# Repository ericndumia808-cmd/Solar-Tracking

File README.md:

solar tracking system
designs by eric

## Collaborators
1. Masika - Supervisor

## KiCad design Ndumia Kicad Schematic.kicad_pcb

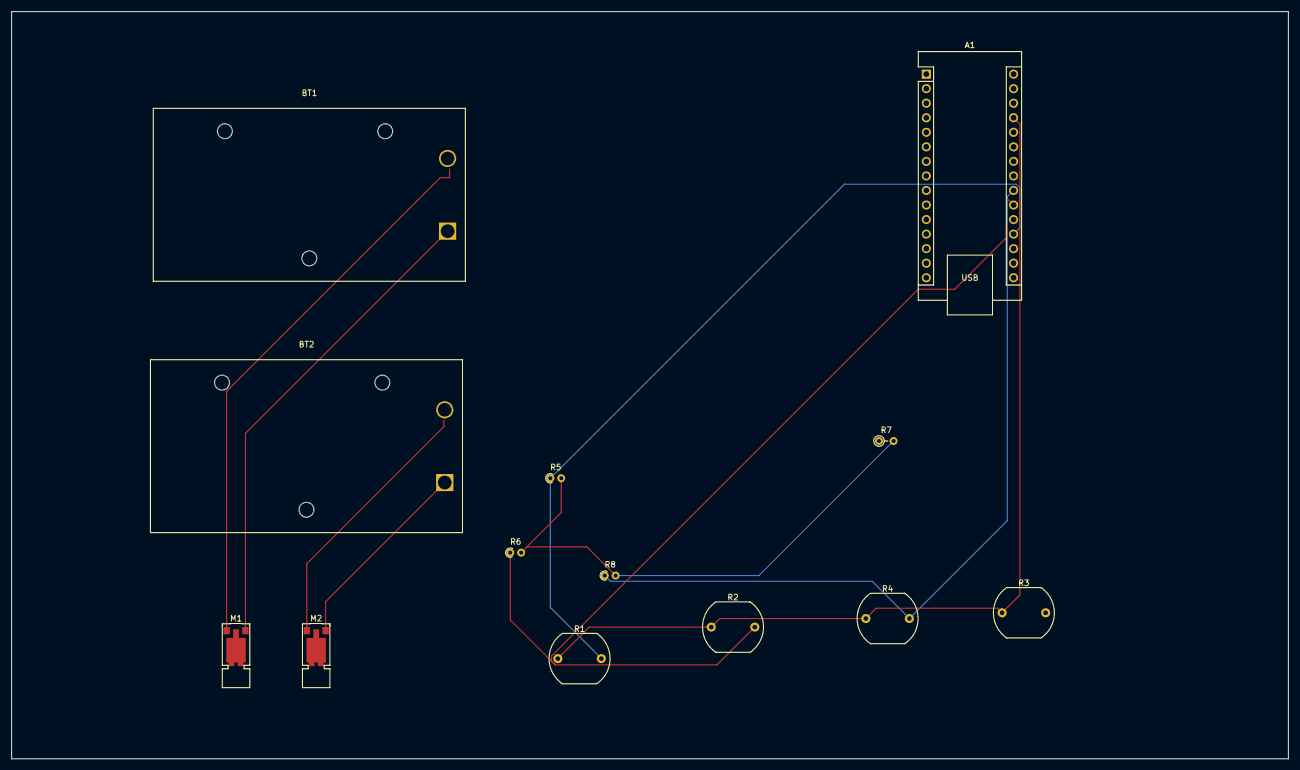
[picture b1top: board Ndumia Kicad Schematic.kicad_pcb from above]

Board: 2 copper layers, 223.0 x 130.5 mm, 13 parts (0 on the bottom side), 8 nets.

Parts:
A1: Arduino_Nano_v2.x; Arduino_Nano
BT1, BT2: Battery; BatteryHolder_Eagle_12BH611-GR
M1, M2: Motor_Servo; Vybronics_VZ30C1T8219732L
R1, R2, R3, R4: LDR03; R_LDR_10x8.5mm_P7.6mm_Vertical
R5, R6, R8: R; R_Axial_DIN0204_L3.6mm_D1.6mm_P1.90mm_Vertical
R7: R; R_Axial_DIN0204_L3.6mm_D1.6mm_P2.54mm_Vertical

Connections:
+5V: A1.27 (+5V), R1.1, R2.1, R3.1, R4.1
GND: A1.29 (GND), R5.2, R6.2, R7.2, R8.2
unnamed: A1.19 (A0), R1.2, R5.1
unnamed: A1.20 (A1), R2.2, R6.1
unnamed: A1.21 (A2), R3.2, R7.1
unnamed: A1.22 (A3), R4.2, R8.1
unnamed: BT1.1 (+), M1.1 (PWM), M1.2 (+)
unnamed: BT2.1 (+), M2.2 (+)
